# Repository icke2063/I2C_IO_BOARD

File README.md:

I2C_IO_BOARD
============

IO Board with I2C connection with behavior like a I2C EEPROM

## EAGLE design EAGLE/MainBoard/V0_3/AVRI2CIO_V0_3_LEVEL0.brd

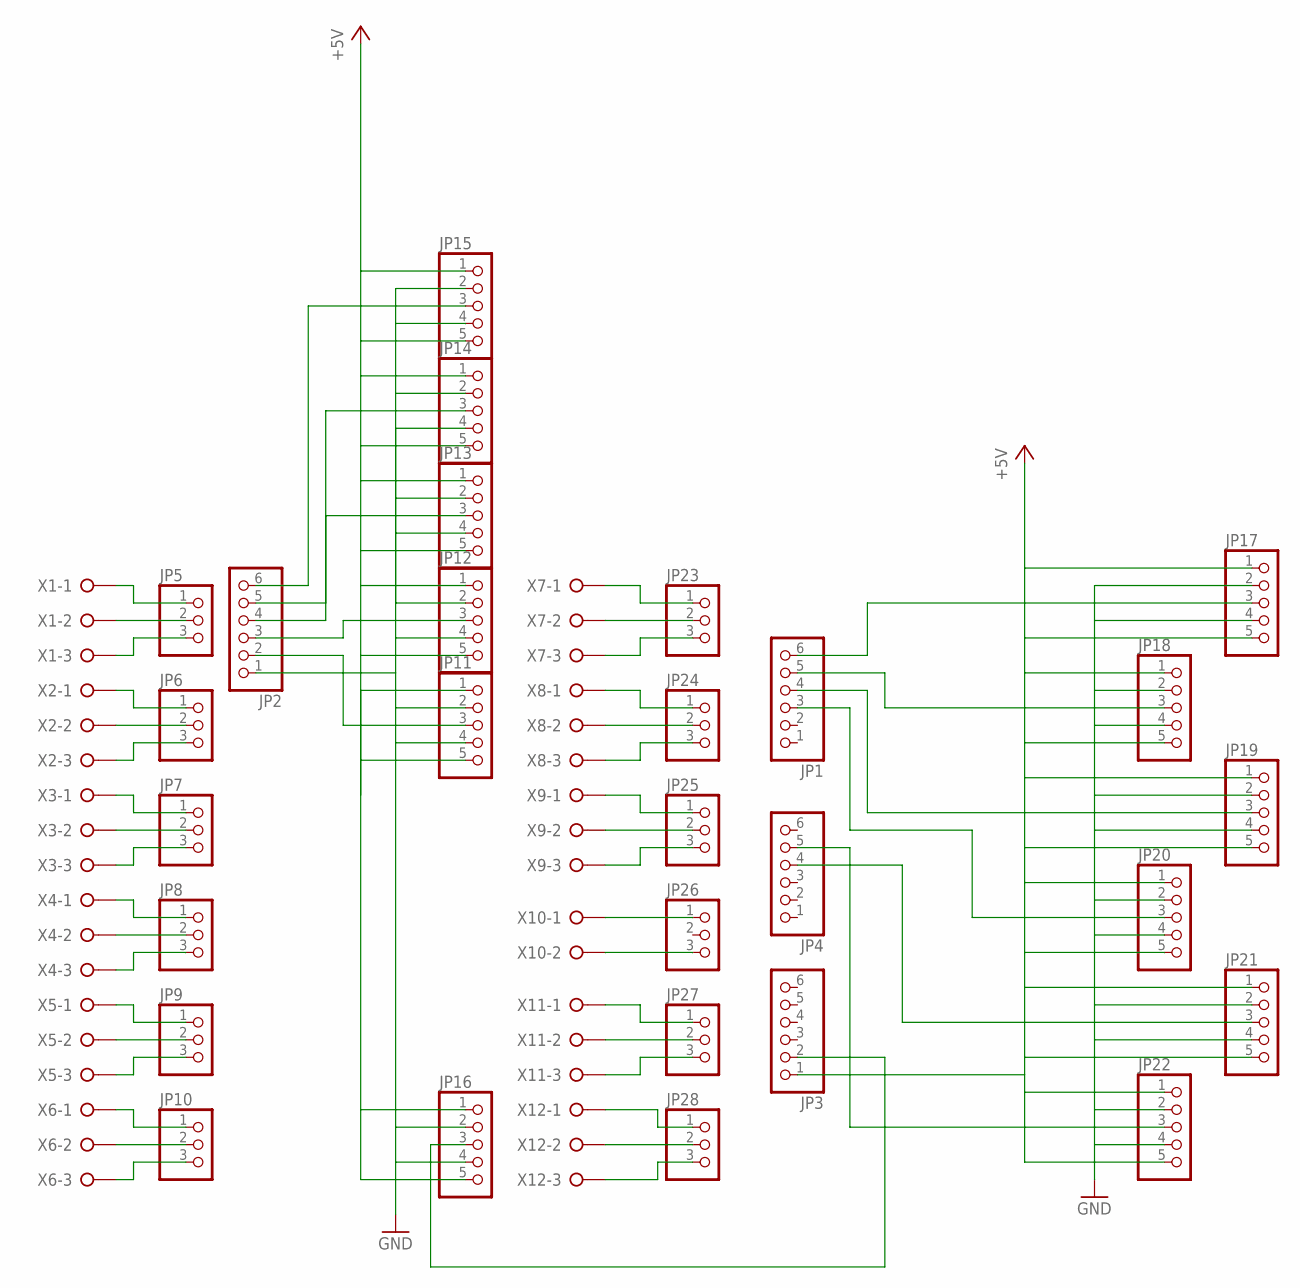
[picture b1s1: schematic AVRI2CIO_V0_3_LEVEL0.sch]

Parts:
JP1, JP2, JP3, JP4: PINHD-1X6; 1X06
JP5, JP6, JP7, JP8, JP9, JP10, JP23, JP24, JP25, JP26, JP27, JP28: PINHD-1X3; 1X03
JP11, JP12, JP13, JP14, JP15, JP16, JP17, JP18, JP19, JP20, JP21, JP22: PINHD-1X5; 1X05
X1, X2, X3, X4, X5, X6, X7, X8, X9, X11, X12: W237-3E
X10: W237-02P; W237-132

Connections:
+5V: JP3.1, JP11.1, JP11.5, JP12.1, JP12.5, JP13.1, JP13.5, JP14.1, JP14.5, JP15.1, JP15.5, JP16.1, JP16.5, JP17.1, JP17.5, JP18.1, JP18.5, JP19.1, JP19.5, JP20.1, JP20.5, JP21.1, JP21.5, JP22.1, JP22.5
GND: JP2.1, JP11.2, JP11.4, JP12.2, JP12.4, JP13.2, JP13.4, JP14.2, JP14.4, JP15.2, JP15.4, JP16.2, JP16.4, JP17.2, JP17.4, JP18.2, JP18.4, JP19.2, JP19.4, JP20.2, JP20.4, JP21.2, JP21.4, JP22.2, JP22.4
unnamed: JP2.2, JP11.3
unnamed: JP2.3, JP12.3
unnamed: JP1.4, JP19.3
unnamed: JP2.4, JP13.3
unnamed: JP2.5, JP14.3
unnamed: JP2.6, JP15.3
unnamed: JP1.6, JP17.3
unnamed: JP1.5, JP18.3
unnamed: JP4.5, JP22.3
unnamed: JP4.4, JP21.3
unnamed: JP3.2, JP16.3
unnamed: JP1.3, JP20.3
unnamed: JP10.2, X6.2
unnamed: JP10.1, X6.1
unnamed: JP10.3, X6.3
unnamed: JP9.3, X5.3
unnamed: JP9.2, X5.2
unnamed: JP9.1, X5.1
unnamed: JP8.3, X4.3
unnamed: JP8.2, X4.2
unnamed: JP8.1, X4.1
unnamed: JP7.3, X3.3
unnamed: JP7.2, X3.2
unnamed: JP7.1, X3.1
unnamed: JP6.3, X2.3
unnamed: JP6.2, X2.2
unnamed: JP6.1, X2.1
unnamed: JP5.3, X1.3
unnamed: JP5.2, X1.2
unnamed: JP5.1, X1.1
unnamed: JP28.3, X12.3
unnamed: JP28.2, X12.2
unnamed: JP28.1, X12.1
unnamed: JP27.3, X11.3
unnamed: JP27.2, X11.2
unnamed: JP27.1, X11.1
unnamed: JP25.3, X9.3
unnamed: JP25.2, X9.2
unnamed: JP25.1, X9.1
unnamed: JP24.3, X8.3
unnamed: JP24.2, X8.2
unnamed: JP24.1, X8.1
unnamed: JP23.3, X7.3
unnamed: JP23.2, X7.2
unnamed: JP23.1, X7.1
unnamed: JP26.1, X10.1
unnamed: JP26.3, X10.2

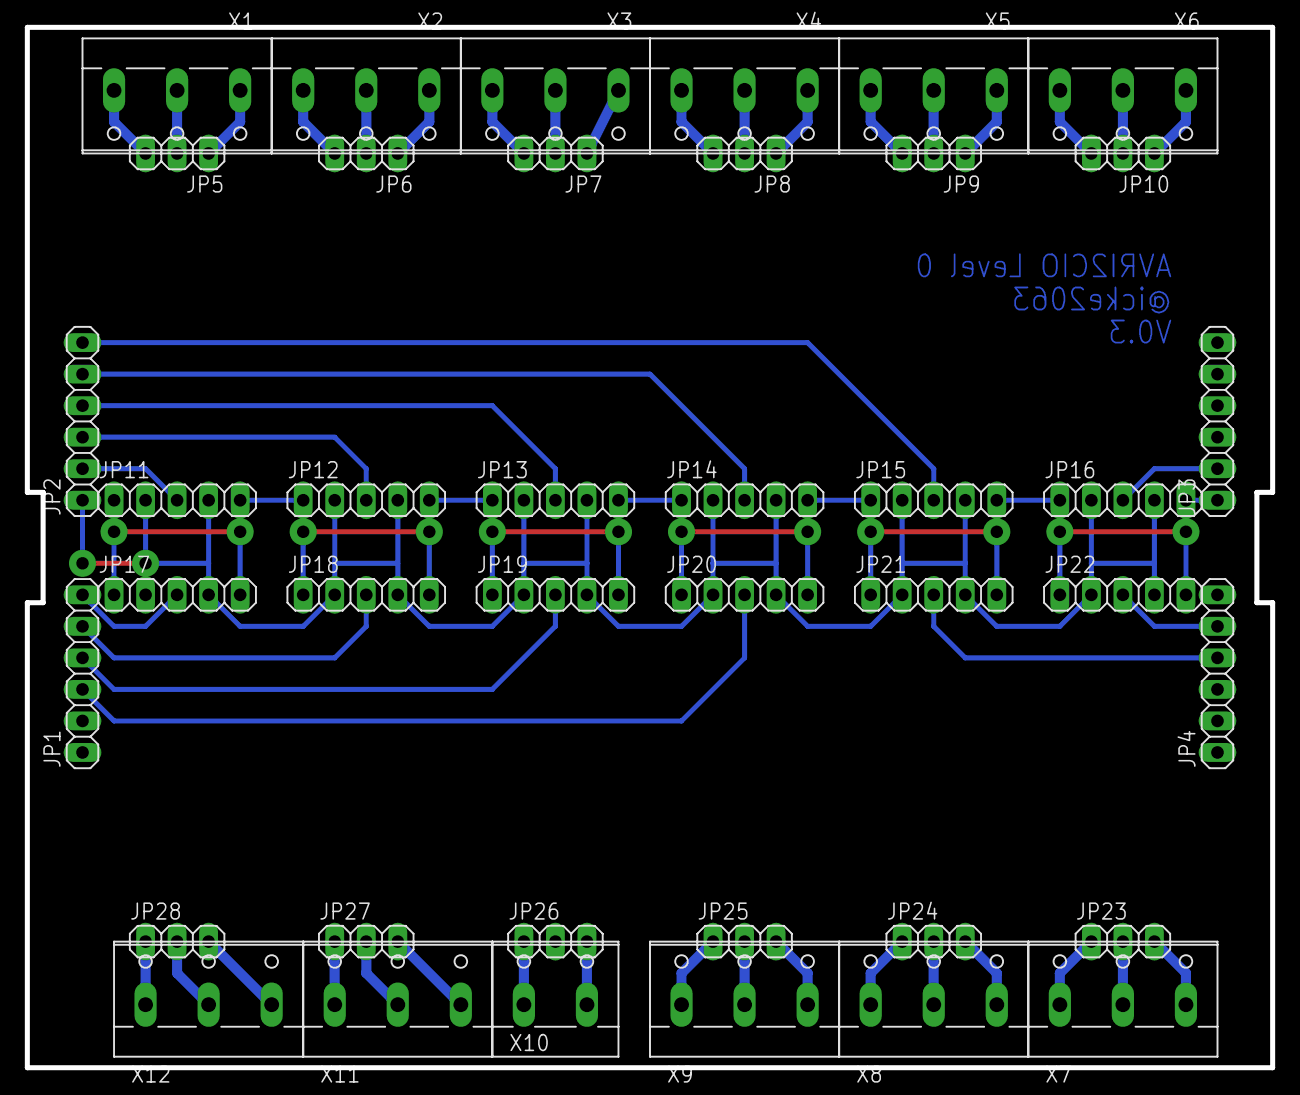
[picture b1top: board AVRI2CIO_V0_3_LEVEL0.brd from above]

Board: 2 copper layers, 100.3 x 83.8 mm, 40 parts (0 on the bottom side), 49 nets.

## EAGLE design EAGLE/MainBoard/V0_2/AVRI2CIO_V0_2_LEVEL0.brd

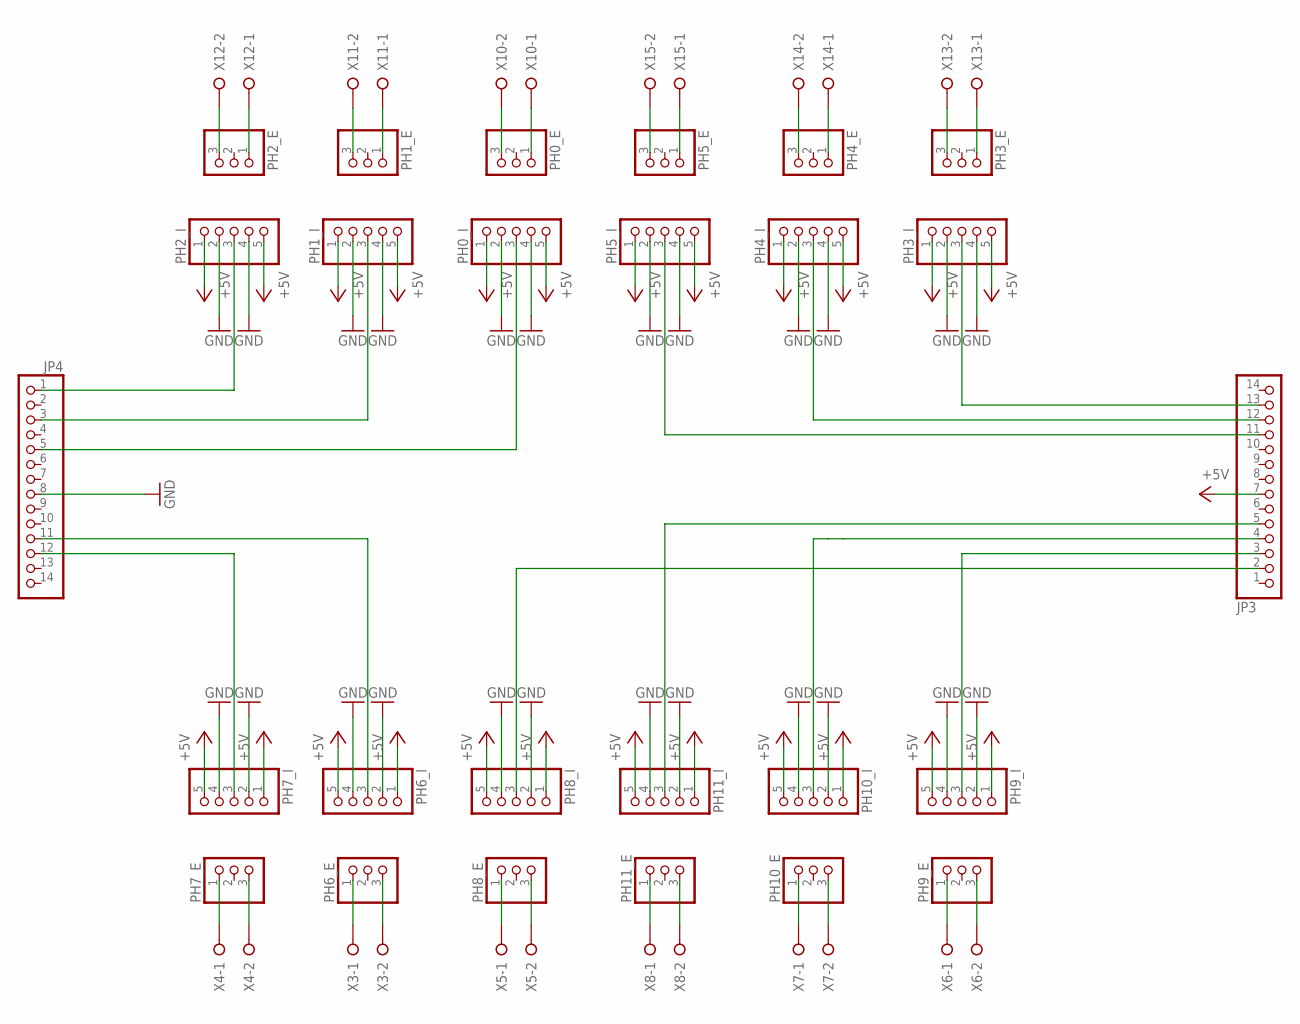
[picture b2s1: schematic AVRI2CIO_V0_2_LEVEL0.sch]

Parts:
JP3, JP4: PINHD-1X14; 1X14
PH0_E, PH1_E, PH2_E, PH3_E, PH4_E, PH5_E, PH6_E, PH7_E, PH8_E, PH9_E, PH10_E, PH11_E: PINHD-1X3; 1X03
PH0_I, PH1_I, PH2_I, PH3_I, PH4_I, PH5_I, PH6_I, PH7_I, PH8_I, PH9_I, PH10_I, PH11_I: PINHD-1X5; 1X05
X3, X4, X5, X6, X7, X8, X10, X11, X12, X13, X14, X15: W237-02P; W237-132

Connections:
+5V: JP3.7, PH0_I.1, PH0_I.5, PH1_I.1, PH1_I.5, PH2_I.1, PH2_I.5, PH3_I.1, PH3_I.5, PH4_I.1, PH4_I.5, PH5_I.1, PH5_I.5, PH6_I.1, PH6_I.5, PH7_I.1, PH7_I.5, PH8_I.1, PH8_I.5, PH9_I.1, PH9_I.5, PH10_I.1, PH10_I.5, PH11_I.1, PH11_I.5
GND: JP4.8, PH0_I.2, PH0_I.4, PH1_I.2, PH1_I.4, PH2_I.2, PH2_I.4, PH3_I.2, PH3_I.4, PH4_I.2, PH4_I.4, PH5_I.2, PH5_I.4, PH6_I.2, PH6_I.4, PH7_I.2, PH7_I.4, PH8_I.2, PH8_I.4, PH9_I.2, PH9_I.4, PH10_I.2, PH10_I.4, PH11_I.2, PH11_I.4
unnamed: PH0_E.3, X10.2
unnamed: PH0_E.1, X10.1
unnamed: PH6_E.3, X3.2
unnamed: PH6_E.1, X3.1
unnamed: PH7_E.3, X4.2
unnamed: PH7_E.1, X4.1
unnamed: PH8_E.3, X5.2
unnamed: PH8_E.1, X5.1
unnamed: PH9_E.3, X6.2
unnamed: PH9_E.1, X6.1
unnamed: PH10_E.3, X7.2
unnamed: PH10_E.1, X7.1
unnamed: PH11_E.3, X8.2
unnamed: PH11_E.1, X8.1
unnamed: JP4.12, PH7_I.3
unnamed: JP3.11, PH5_I.3
unnamed: JP3.3, PH9_I.3
unnamed: PH1_E.1, X11.1
unnamed: PH1_E.3, X11.2
unnamed: JP3.2, PH8_I.3
unnamed: JP3.13, PH3_I.3
unnamed: PH2_E.1, X12.1
unnamed: PH2_E.3, X12.2
unnamed: PH3_E.1, X13.1
unnamed: PH3_E.3, X13.2
unnamed: PH4_E.1, X14.1
unnamed: PH4_E.3, X14.2
unnamed: PH5_E.1, X15.1
unnamed: PH5_E.3, X15.2
unnamed: JP3.12, PH4_I.3
unnamed: JP4.3, PH1_I.3
unnamed: JP4.11, PH6_I.3
unnamed: JP4.5, PH0_I.3
unnamed: JP4.1, PH2_I.3
PD3: JP3.4, PH10_I.3
PD5: JP3.5, PH11_I.3

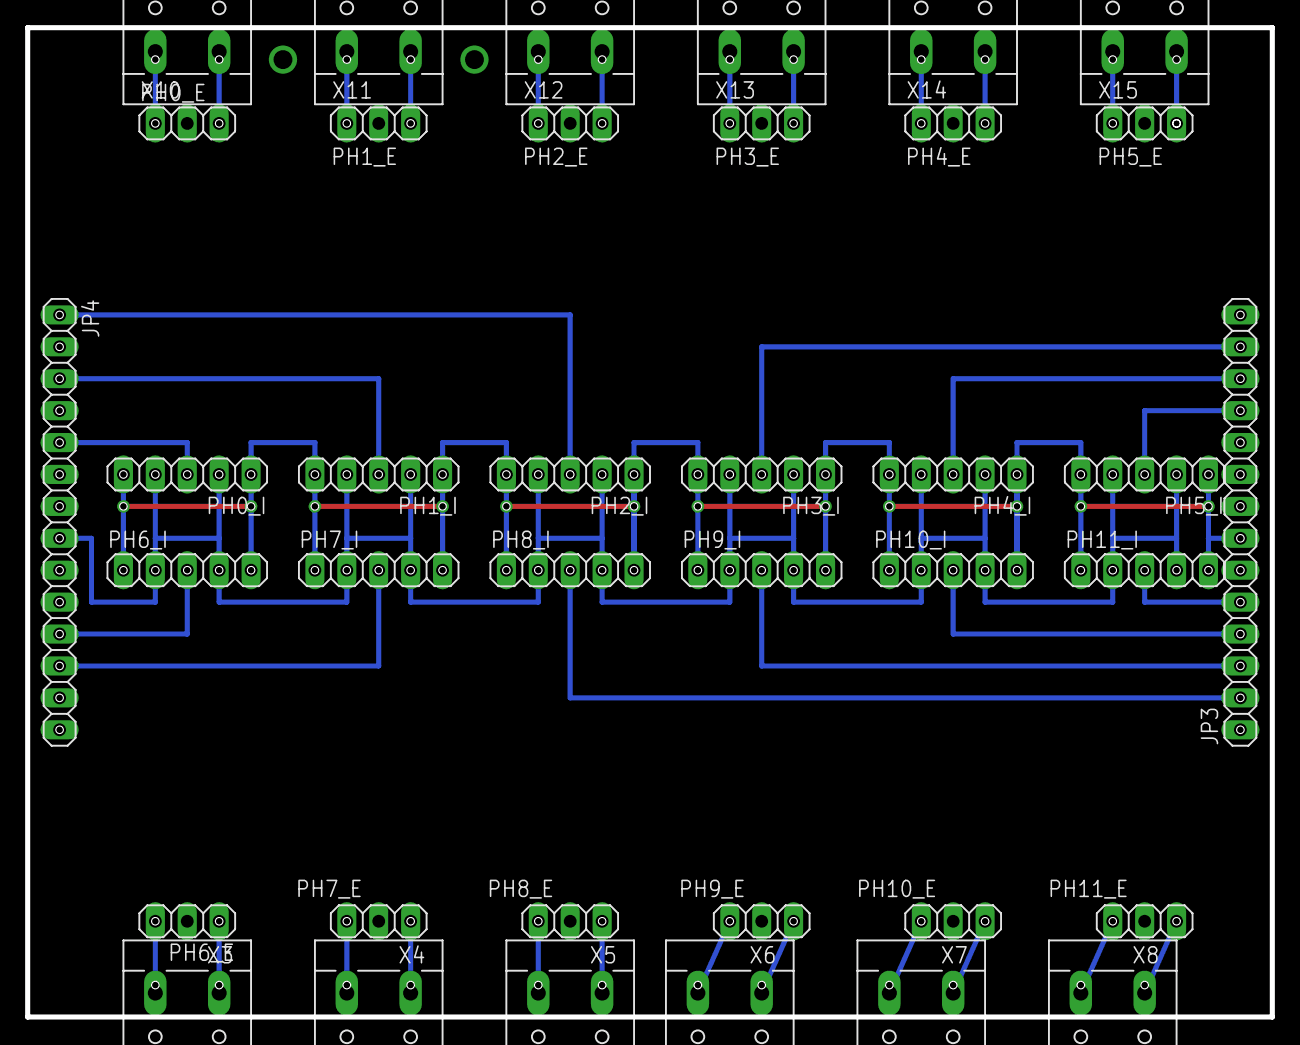
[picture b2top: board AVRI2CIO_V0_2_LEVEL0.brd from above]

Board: 2 copper layers, 99.1 x 78.7 mm, 39 parts (0 on the bottom side), 38 nets.

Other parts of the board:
DRILEGEND: DRILEGEND

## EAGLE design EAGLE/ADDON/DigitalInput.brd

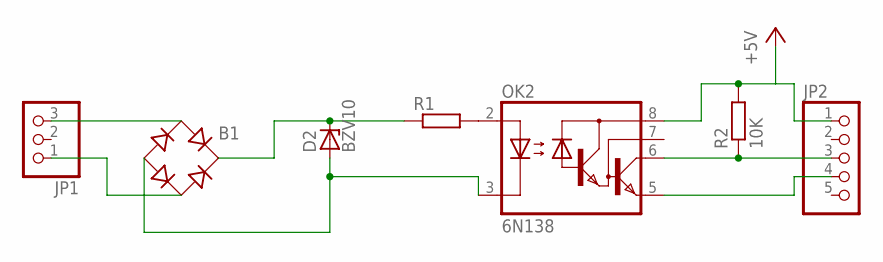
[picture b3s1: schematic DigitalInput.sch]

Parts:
B1: B-DIL
D2: BZV10; DO34Z7
JP1: PINHD-1X3; 1X03
JP2: PINHD-1X5; 1X05
OK2: 6N138; DIL08
R1: R-EU_0204/7; 0204/7
R2: 10K; 0207/5V

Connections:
+5V: JP2.1, OK2.8 (VCC), R2.2
unnamed: JP2.4, OK2.5 (GND)
unnamed: JP2.3, OK2.6 (VO), R2.1
unnamed: B1.AC1, JP1.3
unnamed: B1.AC2, JP1.1
unnamed: OK2.2 (A), R1.2
unnamed: B1.-, D2.A, OK2.3 (C)
unnamed: B1.+, D2.C, R1.1

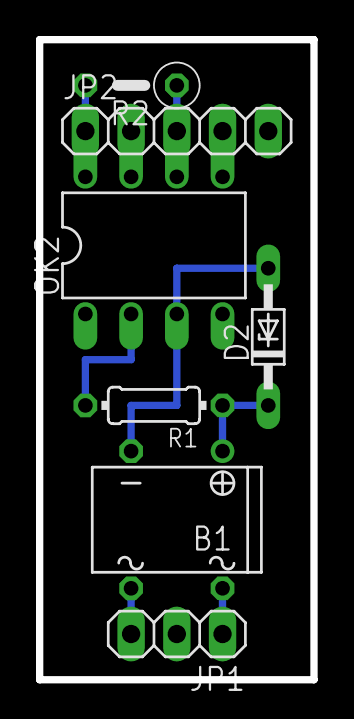
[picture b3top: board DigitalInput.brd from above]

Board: 2 copper layers, 15.2 x 35.6 mm, 7 parts (0 on the bottom side), 8 nets.

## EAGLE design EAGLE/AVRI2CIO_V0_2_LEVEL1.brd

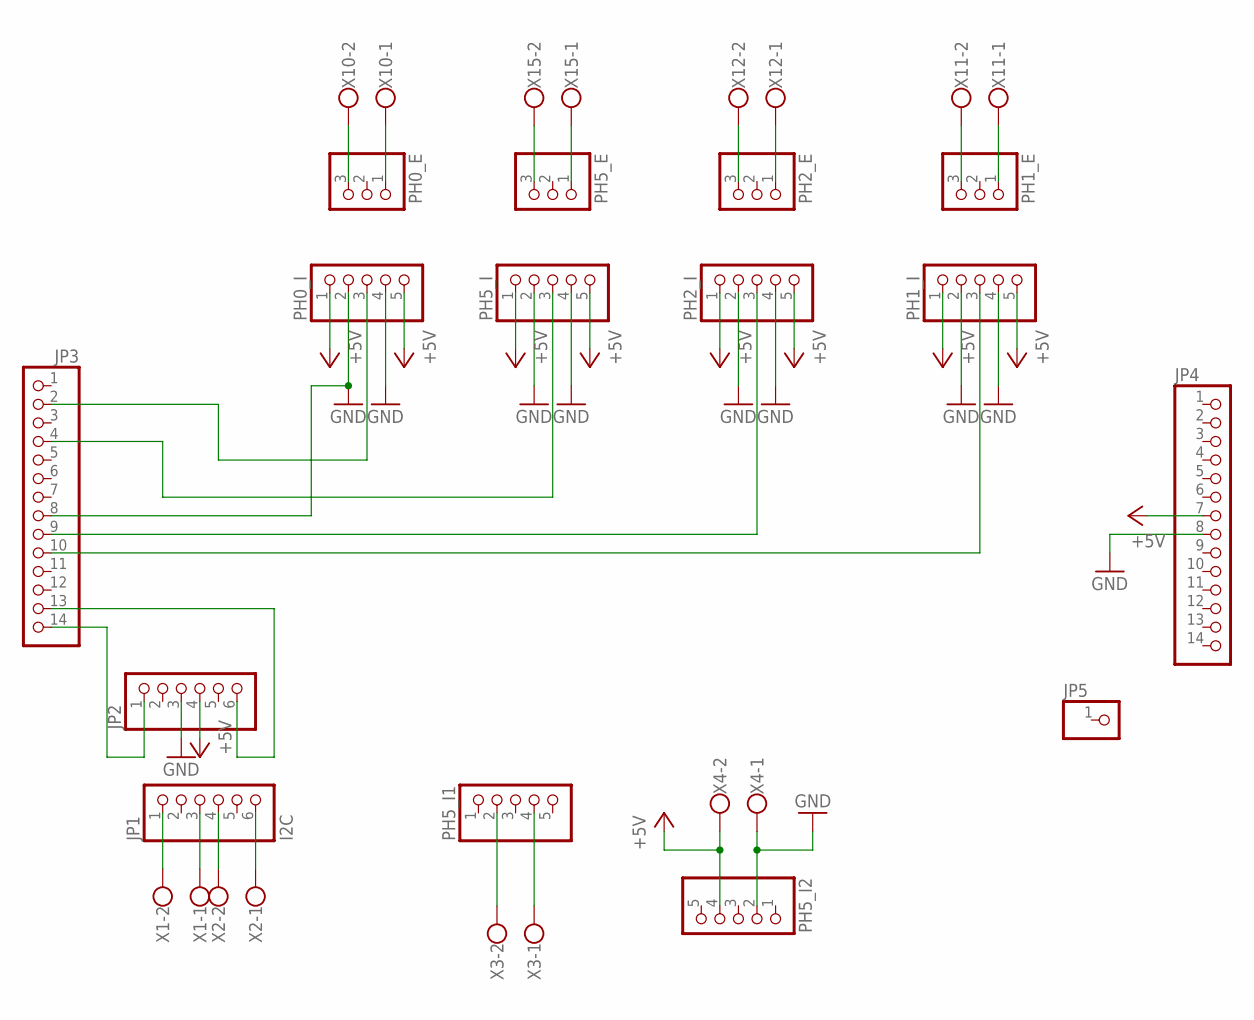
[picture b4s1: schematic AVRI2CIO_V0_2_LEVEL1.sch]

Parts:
JP1: I2C; 1X06
JP2: PINHD-1X6; 1X06
JP3, JP4: PINHD-1X14; 1X14
JP5: PINHD-1X1; 1X01
PH0_E, PH1_E, PH2_E, PH5_E: PINHD-1X3; 1X03
PH0_I, PH1_I, PH2_I, PH5_I, PH5_I1, PH5_I2: PINHD-1X5; 1X05
X1, X2, X3, X4, X11, X12, X15: W237-102
X10: W237-102; MPN 237-102

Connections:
+5V: JP2.4, JP4.7, PH0_I.1, PH0_I.5, PH1_I.1, PH1_I.5, PH2_I.1, PH2_I.5, PH5_I.1, PH5_I.5, PH5_I2.4, X4.2
GND: JP2.3, JP3.8, JP4.8, PH0_I.2, PH0_I.4, PH1_I.2, PH1_I.4, PH2_I.2, PH2_I.4, PH5_I.2, PH5_I.4, PH5_I2.2, X4.1
unnamed: PH0_E.3, X10.2
unnamed: PH0_E.1, X10.1
unnamed: JP3.10, PH1_I.3
unnamed: JP3.9, PH2_I.3
unnamed: JP1.1, X1.2
unnamed: JP1.3, X1.1
unnamed: JP1.4, X2.2
unnamed: JP1.6, X2.1
unnamed: JP2.1, JP3.14
unnamed: JP2.6, JP3.13
unnamed: PH5_I1.2, X3.2
unnamed: PH5_I1.4, X3.1
unnamed: JP3.2, PH0_I.3
unnamed: PH1_E.1, X11.1
unnamed: PH1_E.3, X11.2
unnamed: JP3.4, PH5_I.3
unnamed: PH2_E.1, X12.1
unnamed: PH2_E.3, X12.2
unnamed: PH5_E.1, X15.1
unnamed: PH5_E.3, X15.2

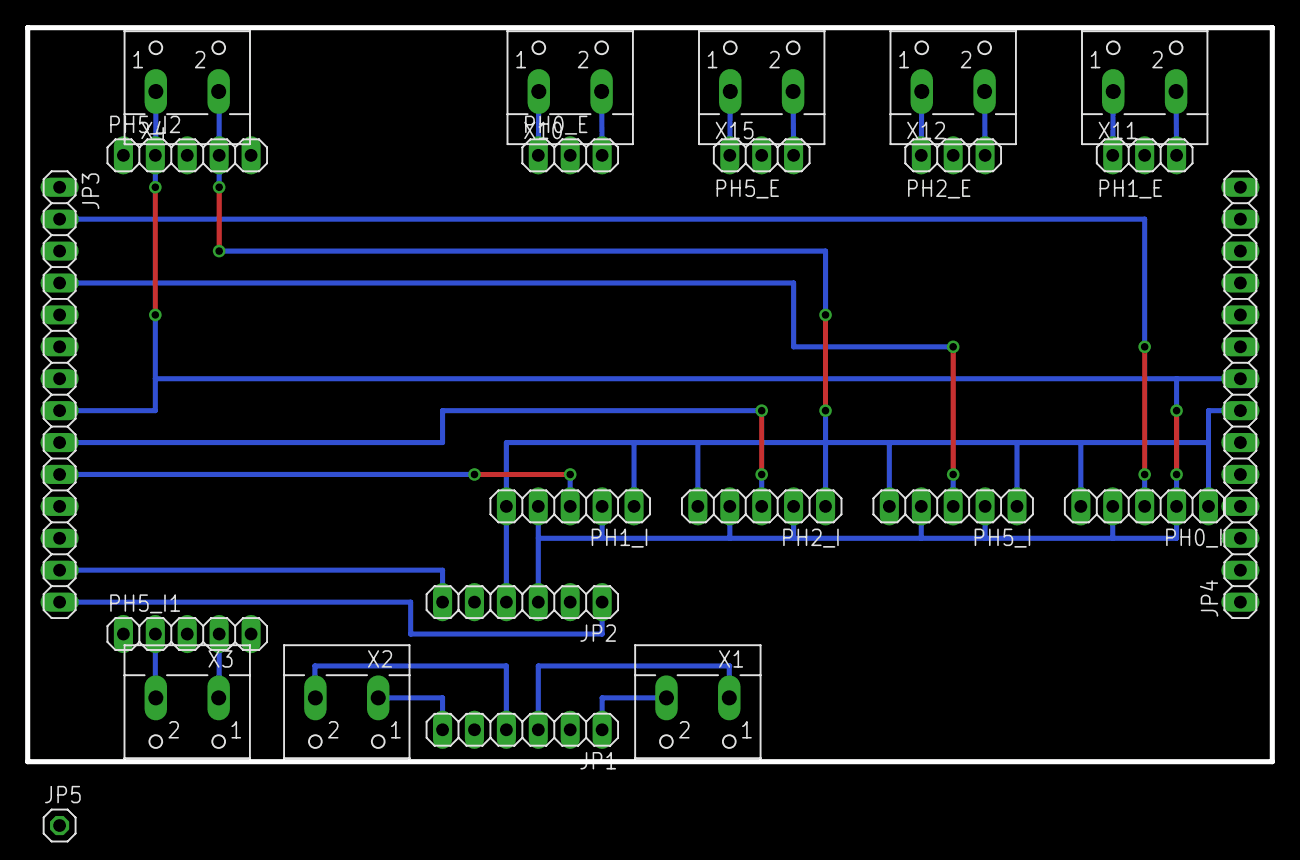
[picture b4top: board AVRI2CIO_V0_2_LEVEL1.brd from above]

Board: 2 copper layers, 99.1 x 58.4 mm, 23 parts (0 on the bottom side), 22 nets.

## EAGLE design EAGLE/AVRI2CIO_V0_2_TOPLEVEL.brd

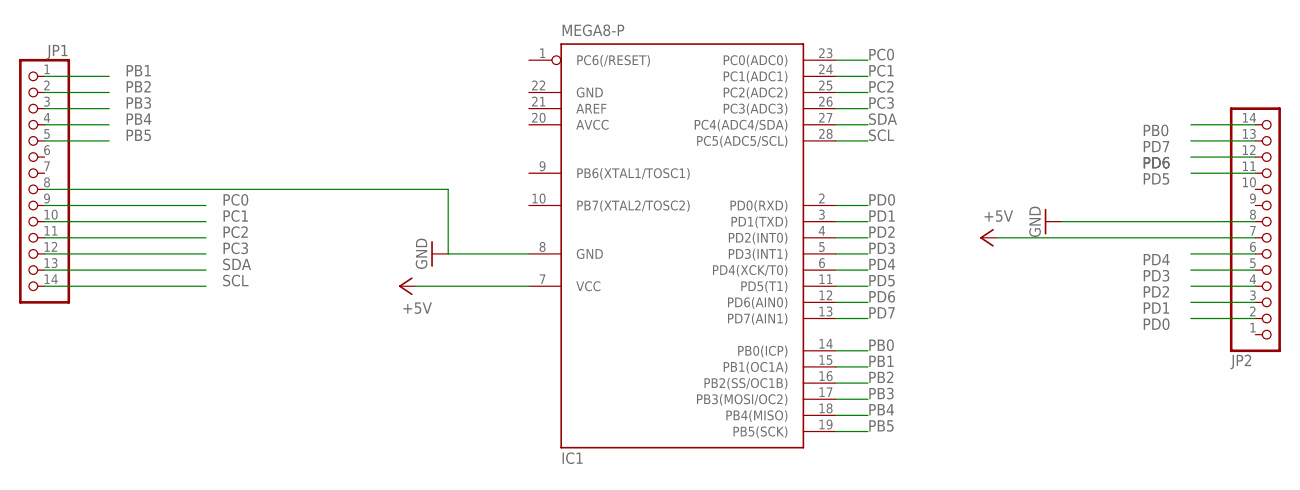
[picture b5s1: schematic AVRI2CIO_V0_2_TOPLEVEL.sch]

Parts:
IC1: MEGA8-P; DIL28-3
JP1, JP2: PINHD-1X14; 1X14

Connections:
+5V: IC1.7 (VCC), JP2.7
AVCC: IC1.20 (AVCC)
GND: IC1.8 (GND), IC1.22 (GND), JP1.8, JP2.8
PB0: IC1.14 (PB0(ICP)), JP2.14
PB1: IC1.15 (PB1(OC1A)), JP1.1
PB2: IC1.16 (PB2(SS/OC1B)), JP1.2
PB3: IC1.17 (PB3(MOSI/OC2)), JP1.3
PB4: IC1.18 (PB4(MISO)), JP1.4
PB5: IC1.19 (PB5(SCK)), JP1.5
PC0: IC1.23 (PC0(ADC0)), JP1.9
PC1: IC1.24 (PC1(ADC1)), JP1.10
PC2: IC1.25 (PC2(ADC2)), JP1.11
PC3: IC1.26 (PC3(ADC3)), JP1.12
PD0: IC1.2 (PD0(RXD)), JP2.2
PD1: IC1.3 (PD1(TXD)), JP2.3
PD2: IC1.4 (PD2(INT0)), JP2.4
PD3: IC1.5 (PD3(INT1)), JP2.5
PD4: IC1.6 (PD4(XCK/T0)), JP2.6
PD5: IC1.11 (PD5(T1)), JP2.11
PD6: IC1.12 (PD6(AIN0)), JP2.12
PD7: IC1.13 (PD7(AIN1)), JP2.13
SCL: IC1.28 (PC5(ADC5/SCL)), JP1.14
SDA: IC1.27 (PC4(ADC4/SDA)), JP1.13

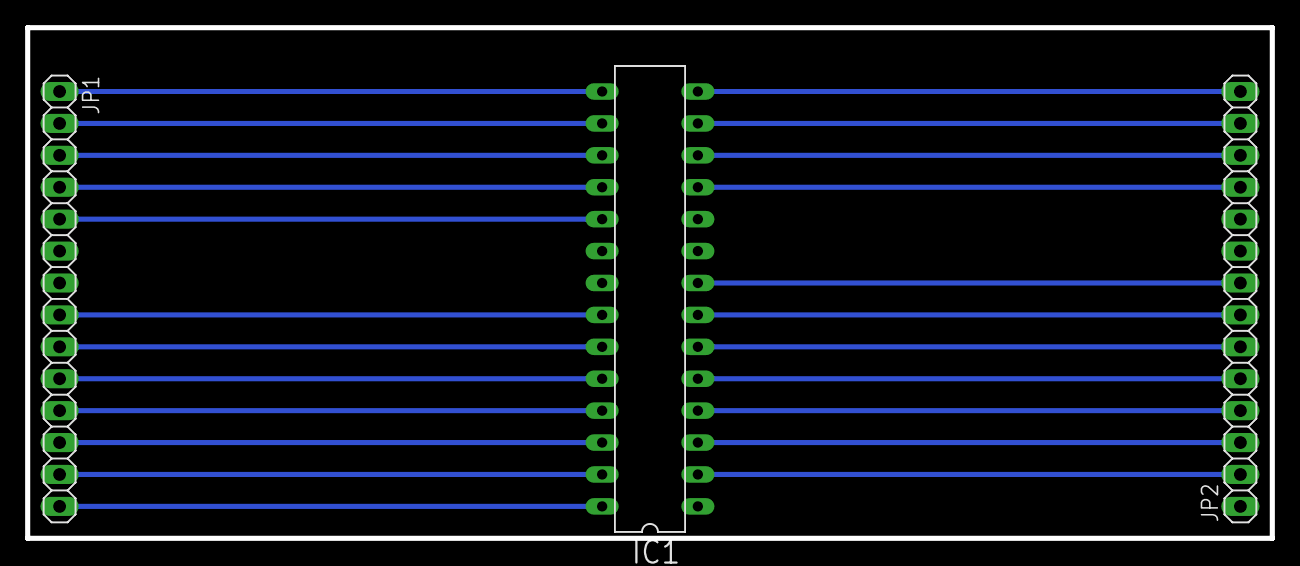
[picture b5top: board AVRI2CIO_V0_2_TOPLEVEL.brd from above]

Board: 2 copper layers, 99.1 x 40.6 mm, 3 parts (0 on the bottom side), 22 nets.

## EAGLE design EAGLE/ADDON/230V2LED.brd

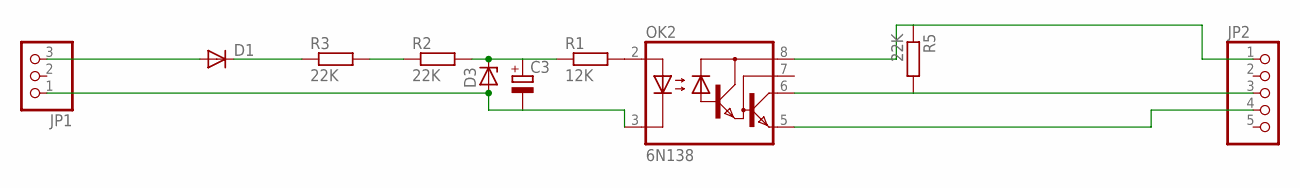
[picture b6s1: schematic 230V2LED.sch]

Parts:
C3: CPOL-EUE2,5-6E; E2,5-6E
D1: DIODE-D-2.5; D-2.5
D3: ZENER-DIODEZD-2.5; ZDIO-2.5
JP1: PINHD-1X3; 1X03
JP2: PINHD-1X5; 1X05
OK2: 6N138; DIL08
R1: 12K; 0207/2V
R2, R3, R5: 22K; 0207/2V

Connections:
unnamed: JP2.1, OK2.8 (VCC), R5.1
unnamed: JP2.4, OK2.5 (GND)
unnamed: JP2.3, OK2.6 (VO), R5.2
unnamed: D1.C, R3.1
unnamed: R2.1, R3.2
unnamed: OK2.2 (A), R1.2
unnamed: D1.A, JP1.3
unnamed: C3.-, D3.A, JP1.1, OK2.3 (C)
unnamed: C3.+, D3.C, R1.1, R2.2

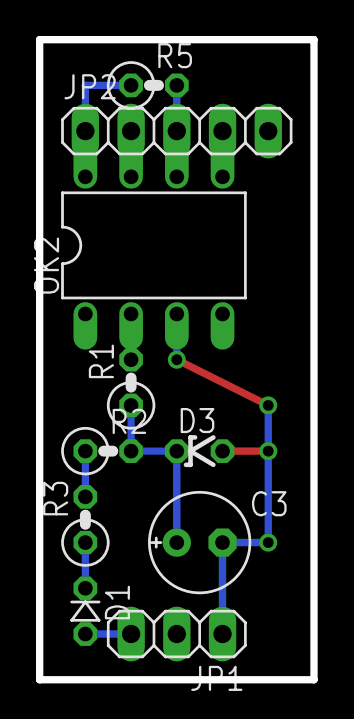
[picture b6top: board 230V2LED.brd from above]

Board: 2 copper layers, 15.2 x 35.6 mm, 10 parts (0 on the bottom side), 9 nets.

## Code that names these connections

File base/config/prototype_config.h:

/********************************************************************************
 Copyright:	icke2063 mailto: icke2063@gmail.com
 @author:	icke2063
 Remarks:
 known Problems: none
 @date:		03.10.2012
 Description:	I2C slave config file

 Dieses Programm ist freie Software. Sie k�nnen es unter den Bedingungen der
 GNU General Public License, wie von der Free Software Foundation ver�ffentlicht,
 weitergeben und/oder modifizieren, entweder gem�� Version 2 der Lizenz oder
 (nach Ihrer Option) jeder sp�teren Version.

 Die Ver�ffentlichung dieses Programms erfolgt in der Hoffnung,
 da� es Ihnen von Nutzen sein wird, aber OHNE IRGENDEINE GARANTIE,
 sogar ohne die implizite Garantie der MARKTREIFE oder der VERWENDBARKEIT
 F�R EINEN BESTIMMTEN ZWECK. Details finden Sie in der GNU General Public License.

 Sie sollten eine Kopie der GNU General Public License zusammen mit diesem
 Programm erhalten haben.
 Falls nicht, schreiben Sie an die Free Software Foundation,
 Inc., 59 Temple Place, Suite 330, Boston, MA 02111-1307, USA.
------------------------------------------------------------------------------*/
#ifndef _SLAVE_CONFIG_H_
#define _SLAVE_CONFIG_H_

#include <avr/io.h>
#include <default_iopin.h>

/// Slave Identification Number
/**
 * This number is used by i2c master to identify this i2c slave as "i2c_io_board"
 */
#define	SLAVE_ID	0x2A
/// default I2C address if value of eeprom is unusable
#define DEFAULT_SLAVE_ADRESSE 0x51
/// count of real useable pins
#define COUNT_IO_PINS 16


/**
 * pin mapping
 * - port pointer	[out]
 * - pin pointer	[in]
 * - ddr pointer
 * - pin number
 */

///UARTTX
#undef UARTTX_PORT
	#define UARTTX_PORT	&PORTD
#undef UARTTX_PIN
	#define UARTTX_PIN	&PIND
#undef UARTTX_DDR
	#define UARTTX_DDR	&DDRD
#undef UARTTX_PINNR
	#define UARTTX_PINNR	PD1

///PIN _0
#undef VIO_PORT_0
	#define VIO_PORT_0	&PORTB
#undef VIO_PIN_0
	#define VIO_PIN_0	&PINB
#undef VIO_DDR_0
	#define VIO_DDR_0	&DDRB
#undef VIO_PINNR_0
	#define VIO_PINNR_0	PD5

///PIN _1
#undef VIO_PORT_1
	#define VIO_PORT_1	&PORTD
#undef VIO_PIN_1
	#define VIO_PIN_1	&PIND
#undef VIO_DDR_1
	#define VIO_DDR_1	&DDRD
#undef VIO_PINNR_1
	#define VIO_PINNR_1	PD7

///PIN _2
#undef VIO_PORT_2
	#define VIO_PORT_2	&PORTB
#undef VIO_PIN_2
	#define VIO_PIN_2	&PINB
#undef VIO_DDR_2
	#define VIO_DDR_2	&DDRB
#undef VIO_PINNR_2
	#define VIO_PINNR_2	PB4

///PIN _3
#undef VIO_PORT_3
	#define VIO_PORT_3	&PORTD
#undef VIO_PIN_3
	#define VIO_PIN_3	&PIND
#undef VIO_DDR_3
	#define VIO_DDR_3	&DDRD
#undef VIO_PINNR_3
	#define VIO_PINNR_3	PD0

///PIN _4
#undef VIO_PORT_4
	#define VIO_PORT_4	&PORTB
#undef VIO_PIN_4
	#define VIO_PIN_4	&PINB
#undef VIO_DDR_4
	#define VIO_DDR_4	&DDRB
#undef VIO_PINNR_4
	#define VIO_PINNR_4	PD3

///PIN _5
#undef VIO_PORT_5
	#define VIO_PORT_5	&PORTD
#undef VIO_PIN_5
	#define VIO_PIN_5	&PIND
#undef VIO_DDR_5
	#define VIO_DDR_5	&DDRD
#undef VIO_PINNR_5
	#define VIO_PINNR_5	PD1

///PIN _6
#undef VIO_PORT_6
	#define VIO_PORT_6	&PORTB
#undef VIO_PIN_6
	#define VIO_PIN_6	&PINB
#undef VIO_DDR_6
	#define VIO_DDR_6	&DDRB
#undef VIO_PINNR_6
	#define VIO_PINNR_6	PB2

///PIN _7
#undef VIO_PORT_7
	#define VIO_PORT_7	&PORTD
#undef VIO_PIN_7
	#define VIO_PIN_7	&PIND
#undef VIO_DDR_7
	#define VIO_DDR_7	&DDRD
#undef VIO_PINNR_7
	#define VIO_PINNR_7	PD2

///PIN _8
#undef VIO_PORT_8
	#define VIO_PORT_8	&PORTB
#undef VIO_PIN_8
	#define VIO_PIN_8	&PINB
#undef VIO_DDR_8
	#define VIO_DDR_8	&DDRB
#undef VIO_PINNR_8
	#define VIO_PINNR_8	PB1

///PIN _9
#undef VIO_PORT_9
	#define VIO_PORT_9	&PORTD
#undef VIO_PIN_9
	#define VIO_PIN_9	&PIND
#undef VIO_DDR_9
	#define VIO_DDR_9	&DDRD
#undef VIO_PINNR_9
	#define VIO_PINNR_9	PD3

///PIN _A
#undef VIO_PORT_A
	#define VIO_PORT_A	&PORTD
#undef VIO_PIN_A
	#define VIO_PIN_A	&PIND
#undef VIO_DDR_A
	#define VIO_DDR_A	&DDRD
#undef VIO_PINNR_A
	#define VIO_PINNR_A	PD5

///PIN _B
#undef VIO_PORT_B
	#define VIO_PORT_B	&PORTD
#undef VIO_PIN_B
	#define VIO_PIN_B	&PIND
#undef VIO_DDR_B
	#define VIO_DDR_B	&DDRD
#undef VIO_PINNR_B
	#define VIO_PINNR_B	PD6

///PIN _C
#undef VIO_PORT_C
	#define VIO_PORT_C	&PORTC
#undef VIO_PIN_C
	#define VIO_PIN_C	&PINC
#undef VIO_DDR_C
	#define VIO_DDR_C	&DDRC
#undef VIO_PINNR_C
	#define VIO_PINNR_C	PC0

///PIN _D
#undef VIO_PORT_D
	#define VIO_PORT_D	&PORTC
#undef VIO_PIN_D
	#define VIO_PIN_D	&PINC
#undef VIO_DDR_D
	#define VIO_DDR_D	&DDRC
#undef VIO_PINNR_D
	#define VIO_PINNR_D	PC1

///PIN _E
#undef VIO_PORT_E
	#define VIO_PORT_E	&PORTC
#undef VIO_PIN_E
	#define VIO_PIN_E	&PINC
#undef VIO_DDR_E
	#define VIO_DDR_E	&DDRC
#undef VIO_PINNR_E
	#define VIO_PINNR_E	PC2

///PIN _F
#undef VIO_PORT_F
	#define VIO_PORT_F	&PORTC
#undef VIO_PIN_F
	#define VIO_PIN_F	&PINC
#undef VIO_DDR_F
	#define VIO_DDR_F	&DDRC
#undef VIO_PINNR_F
	#define VIO_PINNR_F	PC3

#endif //_SLAVE_CONFIG_H

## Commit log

2012-09-27 add 230V2LED Board+Schema add AVRI2CIO Board+Schema
2012-09-30 Schema rename some items Board move some items -> now 12 IO + I2C + Power connectors
2012-09-30 add Board software src folder
2012-10-01 modify eagle item names
2012-10-03 add default I/O usage (by eeprom value)
2012-10-03 add .gitigore
2012-10-15 rearrangement of folder from this version switch/pulse/input functionality should work
2012-10-15 implement S0 function
2013-01-12 .gitignore: add Hexfiles/build folder slave_eeprom_mapping.h: correct comment slave_main: - remove handlePort - modify comments - change on/off on switch functionality - change on/off on pulse functi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
2013-02-01 move to common git repo: - function codes - handle/read virtual IO functions - bit access macros
    modiy main loop for new IO function handling
2013-02-01 add common_AVR submodule
2013-02-01 remove twislave backup
2013-02-01 enable 16bit address support
2013-02-01 commo_AVR makefile modifiations
2013-02-01 add git-version
2013-05-12 update mapping use new mapping change constant buffer_size > BUFFER_SIZE
2013-05-12 update slave_config
2013-05-12 update mapping
2013-05-18 move 230V2LED -> addon dir
2013-05-18 - BUFFER_SIZE -> I2C_BUFFER_SIZE - add debug macro
2013-05-18 - add uart for debug usage - add main debug macro - add printIOsstruct/handle_vio functions
2013-05-18 update submodule common_AVR
2013-06-16 twislave: - change incoming address register byteorder to bigEndian - add some debug output - add 8bit read support - bugfix 1st eeprom byte read access
2013-06-18 - update comments - add getFuncCode function -> change init
2013-06-18 bugfix makefile
2013-06-18 add doxygen file
2013-06-21 update common_AVR
2013-06-21 add AVRI2CIO Version 0.2
2013-09-29 add default virtual io pin header file
2013-09-29 add feature: eeprom write enable
2013-09-29 - add pulse_timeout support (common_AVR) - add automatic uart disable - use new pin information constants - update slave config
2013-09-29 update common_AVR submodule version
2013-09-29 add mapping table (ods)
2013-10-06 chane header
    move SLAVE_ID from slave_config -> slave_eeprom_mapping
2013-12-20 update eagle files
2013-12-20 update config
2014-03-10 update submodule version
2014-05-09 update doku
2014-05-09 add DigitalInput addon board
2014-05-09 update gitignore
2014-05-10 change mapping
    - change virtual data length -> 8 byte (need for onewire romcode)
    - change eeprom data start -> end of mapping
    - change eeprom permanent data length -> 8 byte
    - change function code position -> begin of eeprom
    - change name position
2014-05-10 add onewire support
2014-05-10 update submodule
2014-06-19 [config]change pin number
2014-06-19 update comment
2014-06-19 update version defines
2014-06-19 update mapping comments
2014-06-19 disable TWI debug
2014-06-19 update/enable printIOstruct
2014-06-19 change twi include positions
2014-06-19 change include default_iopin.h position
2014-06-19 remove commented old useless code ;-)
2014-06-19 code cosmetics
2014-06-19 add twi flag to makefile
2014-06-19 update DigitalInput eagle file
2014-07-07 add new config files
2014-07-07 add new debug macros
2014-07-07 use new commonAVR interface
    - use new functions with reduced parameters
    - add some code to find currently handled 1-wire pin,
    needed because of reduced parameter
    - add reset 1-wire data on set new rom code
    - update 1-wire handling
2014-07-07 update sumodule version
2014-07-08 add 1-wire eeprom initialization
2014-07-08 rename address variable
2014-07-08 add changelog
2014-08-06 update prototype config file
2014-08-06 update submodule
    common_AVR
2015-02-13 update makefile
    make cpu frequency variable
2015-02-13 update OW handling
    - add shared memory area
    - disable set1WirePin
    - update read1WirePin
    - update doku
2015-03-05 update 1-wire handling
    - used shared eeprom memory as OW ID storage
2015-07-10 [OW] bugfix main function
2015-07-10 [OW] update main function - change/add debug messages
2015-07-15 update NetIO config
2015-07-15 update debug messages
2016-11-23 [OW] remove set1WirePin
2017-01-07 change submodule url path to relative one
2017-01-07 move eagle files to subfolder
2017-01-07 add eagle file version 0_3
2017-01-11 update AVRI2CIO V0_3
2017-02-17 [EAGLE] move V0_1 to subfolder
2017-02-17 [EAGLE] remove old files
2017-02-17 update comments + little code cosmetics
2017-02-17 update common_AVR submodule
2017-02-17 disable S0 in makefile
2017-02-19 [EAGLE] ignore some errors
